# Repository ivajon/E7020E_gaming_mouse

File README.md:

# Awesome gaming mouse
The awesome gaming mouse project, the one mouse to rule them all. The schematics
are available [here](schematics_and_pcb). The firmware for the mouse is written in rust using [rtic](https://rtic.rs/) and is found [here](code/e7020e_rtic) the rtic app is in the example [rtic_simple_mouse](code/e7020e_rtic/examples/rtic_simple_mouse.rs). The program used to configure the mouse is found [here](code/hosted/rust_version).

## How to flash the mouse
To flash the mouse read [this](e7020e-project/code/e7020_rtic/README.md) to get the build dependecies. When the dependencis are in place it can be built, flashed and run with `cargo run --example rtic_simple_mouse --release`. Note! it can't be built in debug mode since this will create to big of a binary and will not fit on the flash of a stm32f401re.

## Members

- Erik Serrander
- eriser-8@student.ltu.se
  
- Ivar Jönsson
- ivajns-9@student.ltu.se

## High level specification

### Basic
- [x] Left and right click
- [x] relative position

### Higher
- [x] scroll wheel
- [x] macro system
- [x] Side buttons

### Stretch
- [x] Computer communication
- [ ] LEDs, i.e. debug/ui
- [ ] Rumble motor
- [ ] Perfect spray

### Implementation
- Unit testing
- Cuntinuous integration

# Specifications
## Mouse buttons
The buttons used are [D2F-01F](https://www.elfa.se/sv/mikrobrytare-d2f-100ma-1co-74n-kolv-omron-electronic-components-d2f-01f/p/11082662?track=true&no-cache=true&marketingPopup=false) since these are well regarded by users.
We have decided to have 4 main buttons on the mouse, 2 on the front and 2 on the side.
## Side buttons 

To reduce the bouncing of the buttons a 10u capacitor is places to ground from the signal trace. This will allow the signal to be pulled low for high frequencies. 

To drive the buttons a 5v voltage is used with a series resistor of 4.7 k to limit the current to close to 1mA. The mosfet used to limit the output acts as a decoupler thus not draining anny current ( in theory ).

## Front buttons

## Mouse wheel

The [mouse wheel](https://se.rs-online.com/web/p/mechanical-rotary-encoders/7295545) is also debounced using the same capacitor values as the mouse button. This should not be as needed but better safe than sorry.

The mouse wheel also uses the same nfet to step down the voltage.

## Rumble motor

## Main board

## Case 
We will base our case on this moddel of the [g305](https://www.thingiverse.com/thing:3969266)
with this [base](https://www.thingiverse.com/thing:3564894).

The stl files can be found in our [model folder](model/).

## Grading

- Erik Serrander
  - Expected contributions towards grade 4
    - side buttons
    - diodes
  - Expected contributions towards grade 5
    - Computer communication
    - Rumble motor
  
- Ivar Jönsson
  - Expected contributions towards grade 4
    - PCB layout
      - Itterative design using a 3d printer to validate pcb fitting and footprint layout
      - Ease of assembly
    - Case customization 
      - Mountingholes and posibility to use a usb cable
    - Mouse wheel
      - Selecting a rotary encoder
    - diodes
      - status LEDs to validate voltage sections
  - Expected contributions towards grade 5
    - Computer communication
    - DPI configuration
    - Perfect spray
      - This might not be applicable. 

## contributions

- Erik Serrander
  - Hardware design (werry minor)
  - Macro system
  - Macro system config mouse side
  - Mouse state software (major)

- Ivar Jönsson
  - Hardware design (allmost all)
  - Macro system config pc side
  - Mouse state software (minor)
  - Enclosure manufacturing

- Togheter / both
  - Init code
  - Interuppt handlers
  - Harware assembly

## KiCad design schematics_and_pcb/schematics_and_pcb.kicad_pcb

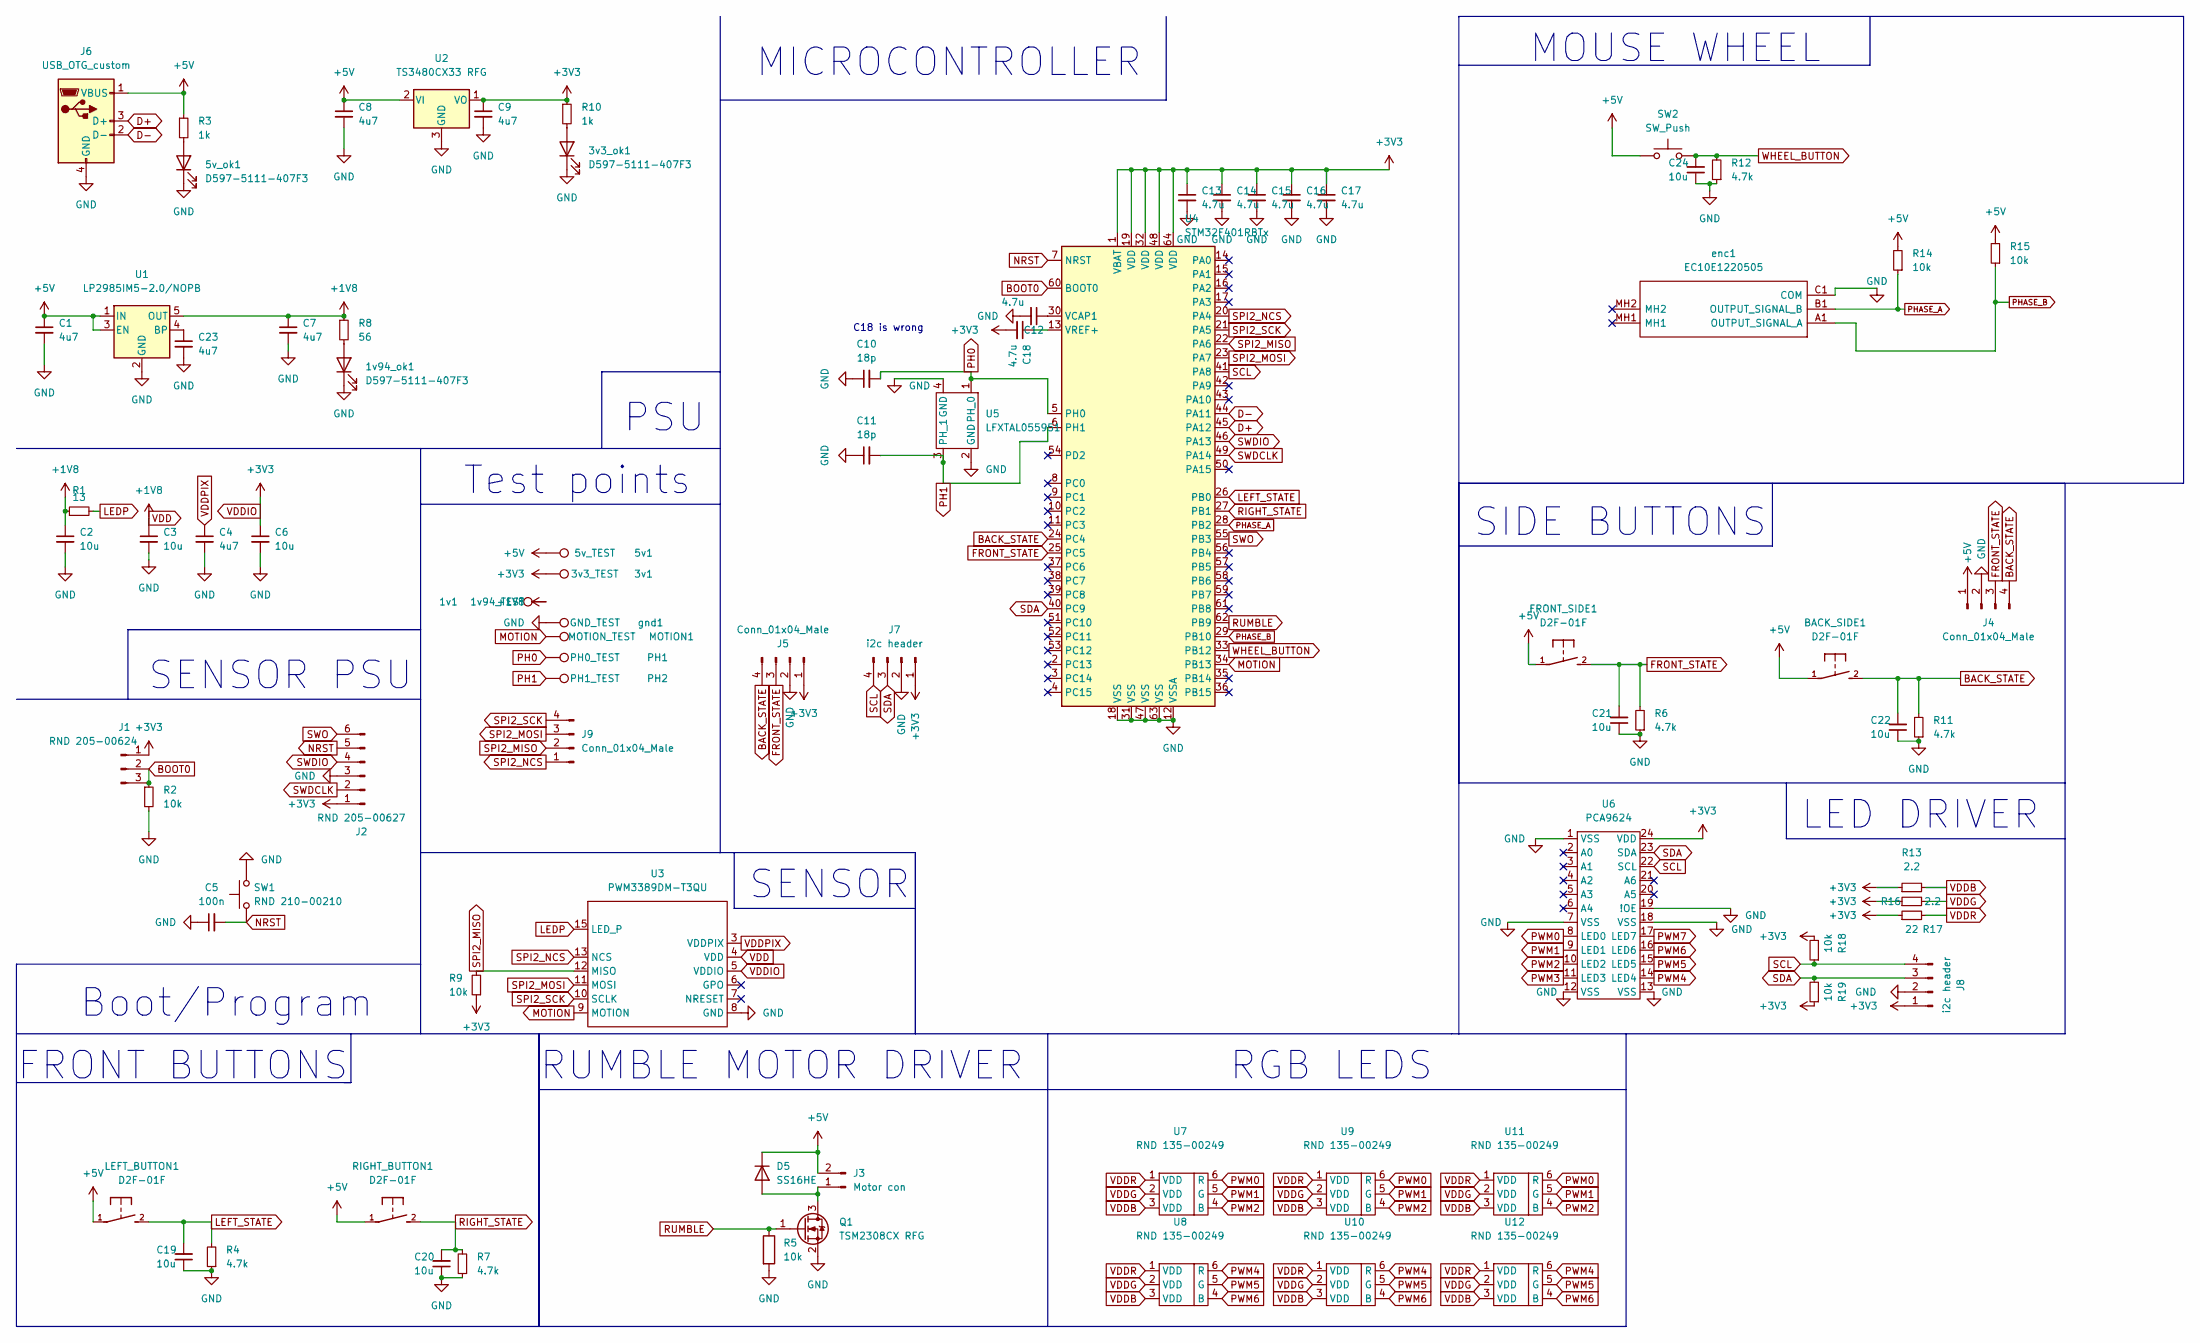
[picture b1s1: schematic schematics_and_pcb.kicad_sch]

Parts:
1v1: 1v94_TEST; PinHeader_1x01_P2.54mm_Vertical
1v94_ok1, 3v3_ok1, 5v_ok1: D597-5111-407F3; LED_0805_2012Metric_Pad1.15x1.40mm_HandSolder; part # D597-5111-407F3
3v1: 3v3_TEST; PinHeader_1x01_P2.54mm_Vertical
5v1: 5v_TEST; PinHeader_1x01_P2.54mm_Vertical
BACK_SIDE1: D2F-01F
C1, C4, C7, C8, C9, C23: 4u7; C_0805_2012Metric_Pad1.18x1.45mm_HandSolder
C2, C3, C6, C19, C20, C21, C22, C24: 10u; C_0805_2012Metric_Pad1.18x1.45mm_HandSolder
C5: 100n; C_0805_2012Metric_Pad1.18x1.45mm_HandSolder
C10, C11: 18p; C_0805_2012Metric_Pad1.18x1.45mm_HandSolder
C12, C13, C14, C15, C16, C17, C18: 4.7u; C_0805_2012Metric_Pad1.18x1.45mm_HandSolder
D5: SS16HE; SOD-323HE; part # SS16HE
FRONT_SIDE1: D2F-01F
J1: RND 205-00624; PinHeader_1x03_P2.54mm_Vertical
J2: RND 205-00627; PinHeader_1x06_P2.54mm_Vertical
J3: Motor con; PinSocket_1x02_P2.54mm_Vertical
J4, J5: Conn_01x04_Male; PinHeader_1x04_P2.54mm_Vertical
J6: USB_OTG_custom; USB_2.45
J7, J8: i2c header; PinHeader_1x04_P2.54mm_Vertical
J9: Conn_01x04_Male; PinHeader_1x04_P1.00mm_Vertical
LEFT_BUTTON1: D2F-01F; part # D2F-01F
MOTION1: MOTION_TEST; PinHeader_1x01_P2.54mm_Vertical
PH1: PH0_TEST; PinHeader_1x01_P2.54mm_Vertical
PH2: PH1_TEST; PinHeader_1x01_P2.54mm_Vertical
Q1: TSM2308CX RFG; SOT-23; part # TSM2308CX RFG
R1: 13; R_0805_2012Metric_Pad1.20x1.40mm_HandSolder; part # RND 155HP05W3F130JT5E
R2, R9, R14, R15, R18, R19: 10k; R_0805_2012Metric_Pad1.20x1.40mm_HandSolder; part # RT0805FRE0710KL
R3, R10: 1k; R_0805_2012Metric_Pad1.20x1.40mm_HandSolder; part # RC0805FR-071KL
R4, R6, R7, R11, R12: 4.7k; R_0805_2012Metric_Pad1.20x1.40mm_HandSolder; part # RC0805FR-074K7L
R5: 10k; R_0805_2012Metric_Pad1.20x1.40mm_HandSolder; part # RC0805FR-071KL
R8: 56; R_0805_2012Metric_Pad1.20x1.40mm_HandSolder; part # RND 155HP05W3F560JT5E
R13, R16: 2.2; R_0805_2012Metric_Pad1.20x1.40mm_HandSolder
R17: 22; R_0805_2012Metric_Pad1.20x1.40mm_HandSolder
RIGHT_BUTTON1: D2F-01F; part # D2F-01F
SW1: RND 210-00210; SW_Push_1P1T_NO_6x6mm_H9.5mm
SW2: SW_Push; evqP0E07; part # evqP0E07
U1: LP2985IM5-2.0/NOPB; SOT-23-5; part # LP2985IM5-2.0/NOPB
U2: TS3480CX33 RFG; SOT-23; part # TS3480CX33 RFG
U3: PWM3389DM-T3QU; PMW3389DM-T3QU; part # PWM3389DM-T3QU
U4: STM32F401RBTx; LQFP-64_10x10mm_P0.5mm
U5: LFXTAL055951
U6: PCA9624; TSSOP-24
U7, U8, U9, U10, U11, U12: RND 135-00249; RND_135-00249
enc1: EC10E1220505; Manufacturer_Part_Number EC10E1220505; Mouser Part Number 688-EC10E1220505
gnd1: GND_TEST; PinHeader_1x01_P2.54mm_Vertical

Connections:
+5V: 5v1.1, BACK_SIDE1.1, C1.1, C8.1, D5.1 (K), FRONT_SIDE1.1, J3.2, J4.1, J6.1 (VBUS), LEFT_BUTTON1.1, R3.1, R14.2, R15.2, RIGHT_BUTTON1.1, SW2.1, U1.1 (IN), U1.3 (EN), U2.2 (VI)
BACK_STATE: BACK_SIDE1.2, C22.2, J4.4, J5.4, R11.2, U4.24 (PC4)
BOOT0: J1.2, J1.3, R2.1, U4.60 (BOOT0)
D+: J6.3 (D+), U4.45 (PA12)
D-: J6.2 (D-), U4.44 (PA11)
FRONT_STATE: C21.2, FRONT_SIDE1.2, J4.3, J5.3, R6.2, U4.25 (PC5)
GND: 1v94_ok1.1 (K), 3v3_ok1.1 (K), 5v_ok1.1 (K), C1.2, C2.2, C3.2, C4.2, C5.1, C6.2, C7.2, C8.2, C9.2, C10.1, C11.1, C12.2, C13.2, C14.2, C15.2, C16.2, C17.2, C19.1, C20.1, C21.1, C22.1, C23.2, C24.1, J2.3, J4.2, J5.2, J6.4 (GND), J7.2, J8.2, Q1.2 (S), R2.2, R4.1, R5.2, R6.1, R7.1, R11.1, R12.1, SW1.2, U1.2 (GND), U2.3 (GND), U3.8 (GND), U4.12 (VSSA), U4.18 (VSS), U4.31 (VSS), U4.47 (VSS), U4.63 (VSS), U5.2 (GND), U5.4 (GND), U6.1 (VSS), U6.7 (VSS), U6.12 (VSS), U6.13 (VSS), U6.18 (VSS), U6.19 (!OE), enc1.C1 (COM), gnd1.1
LEDP: R1.2, U3.15 (LED_P)
LEFT_STATE: C19.2, LEFT_BUTTON1.2, R4.2, U4.26 (PB0)
MOTION: MOTION1.1, U3.9 (MOTION), U4.34 (PB13)
NRST: C5.2, J2.5, SW1.1, U4.7 (NRST)
unnamed: 1v94_ok1.2 (A), R8.2
unnamed: 3v3_ok1.2 (A), R10.2
unnamed: 5v_ok1.2 (A), R3.2
unnamed: C12.1, U4.30 (VCAP1)
unnamed: C18.1, U4.13 (VREF+)
unnamed: C23.1, U1.4 (BP)
unnamed: D5.2 (A), J3.1, Q1.3 (D)
PH0: C10.2, PH1.1, U4.5 (PH0), U5.1 (PH_0)
PH1: C11.2, PH2.1, U4.6 (PH1), U5.3 (PH_1)
PHASE_A: R14.1, U4.28 (PB2), enc1.B1 (OUTPUT_SIGNAL_B)
PHASE_B: R15.1, U4.29 (PB10), enc1.A1 (OUTPUT_SIGNAL_A)
PWM0: U6.8 (LED0), U7.6 (R), U9.6 (R), U11.6 (R)
PWM1: U6.9 (LED1), U7.5 (G), U9.5 (G), U11.5 (G)
PWM2: U6.10 (LED2), U7.4 (B), U9.4 (B), U11.4 (B)
PWM3: U6.11 (LED3)
PWM4: U6.14 (LED4), U8.6 (R), U10.6 (R), U12.6 (R)
PWM5: U6.15 (LED5), U8.5 (G), U10.5 (G), U12.5 (G)
PWM6: U6.16 (LED6), U8.4 (B), U10.4 (B), U12.4 (B)
PWM7: U6.17 (LED7)
RIGHT_STATE: C20.2, R7.2, RIGHT_BUTTON1.2, U4.27 (PB1)
RUMBLE: Q1.1 (G), R5.1, U4.62 (PB9)
SCL: J7.4, J8.4, R18.1, U4.41 (PA8), U6.22 (SCL)
SDA: J7.3, J8.3, R19.2, U4.40 (PC9), U6.23 (SDA)
SPI2_MISO: J9.2, R9.2, U3.12 (MISO), U4.22 (PA6)
SPI2_MOSI: J9.3, U3.11 (MOSI), U4.23 (PA7)
SPI2_NCS: J9.1, U3.13 (NCS), U4.20 (PA4)
SPI2_SCK: J9.4, U3.10 (SCLK), U4.21 (PA5)
SWDCLK: J2.2, U4.49 (PA14)
SWDIO: J2.4, U4.46 (PA13)
SWO: J2.6, U4.55 (PB3)
VDD: 1v1.1, C2.1, C3.1, C7.1, R1.1, R8.1, U1.5 (OUT), U3.4 (VDD)
VDDB: R13.2, U7.3 (VDD), U8.3 (VDD), U9.3 (VDD), U10.3 (VDD), U11.3 (VDD), U12.3 (VDD)
VDDG: R16.2, U7.2 (VDD), U8.2 (VDD), U9.2 (VDD), U10.2 (VDD), U11.2 (VDD), U12.2 (VDD)
VDDIO: 3v1.1, C6.1, C9.1, C13.1, C14.1, C15.1, C16.1, C17.1, C18.2, J1.1, J2.1, J5.1, J7.1, J8.1, R9.1, R10.1, R13.1, R16.1, R17.1, R18.2, R19.1, U2.1 (VO), U3.5 (VDDIO), U4.1 (VBAT), U4.19 (VDD), U4.32 (VDD), U4.48 (VDD), U4.64 (VDD), U6.24 (VDD)
VDDPIX: C4.1, U3.3 (VDDPIX)
VDDR: R17.2, U7.1 (VDD), U8.1 (VDD), U9.1 (VDD), U10.1 (VDD), U11.1 (VDD), U12.1 (VDD)
WHEEL_BUTTON: C24.2, R12.2, SW2.2, U4.33 (PB12)

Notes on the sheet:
LED DRIVER
Test points
PSU
SENSOR
C18 is wrong
FRONT BUTTONS
Boot/Program
SENSOR PSU
RGB LEDS
MICROCONTROLLER
RUMBLE MOTOR DRIVER
MOUSE WHEEL
SIDE BUTTONS

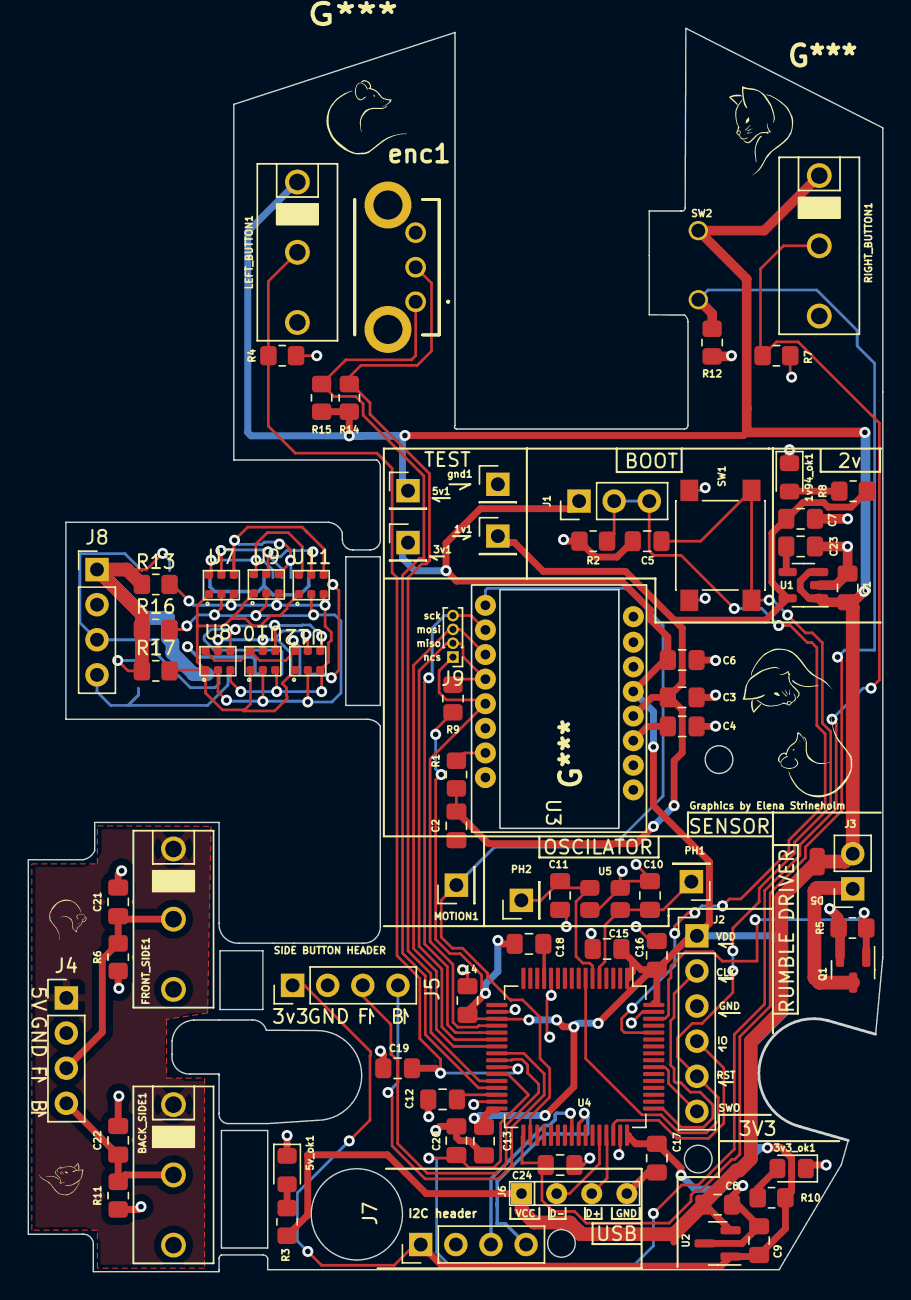
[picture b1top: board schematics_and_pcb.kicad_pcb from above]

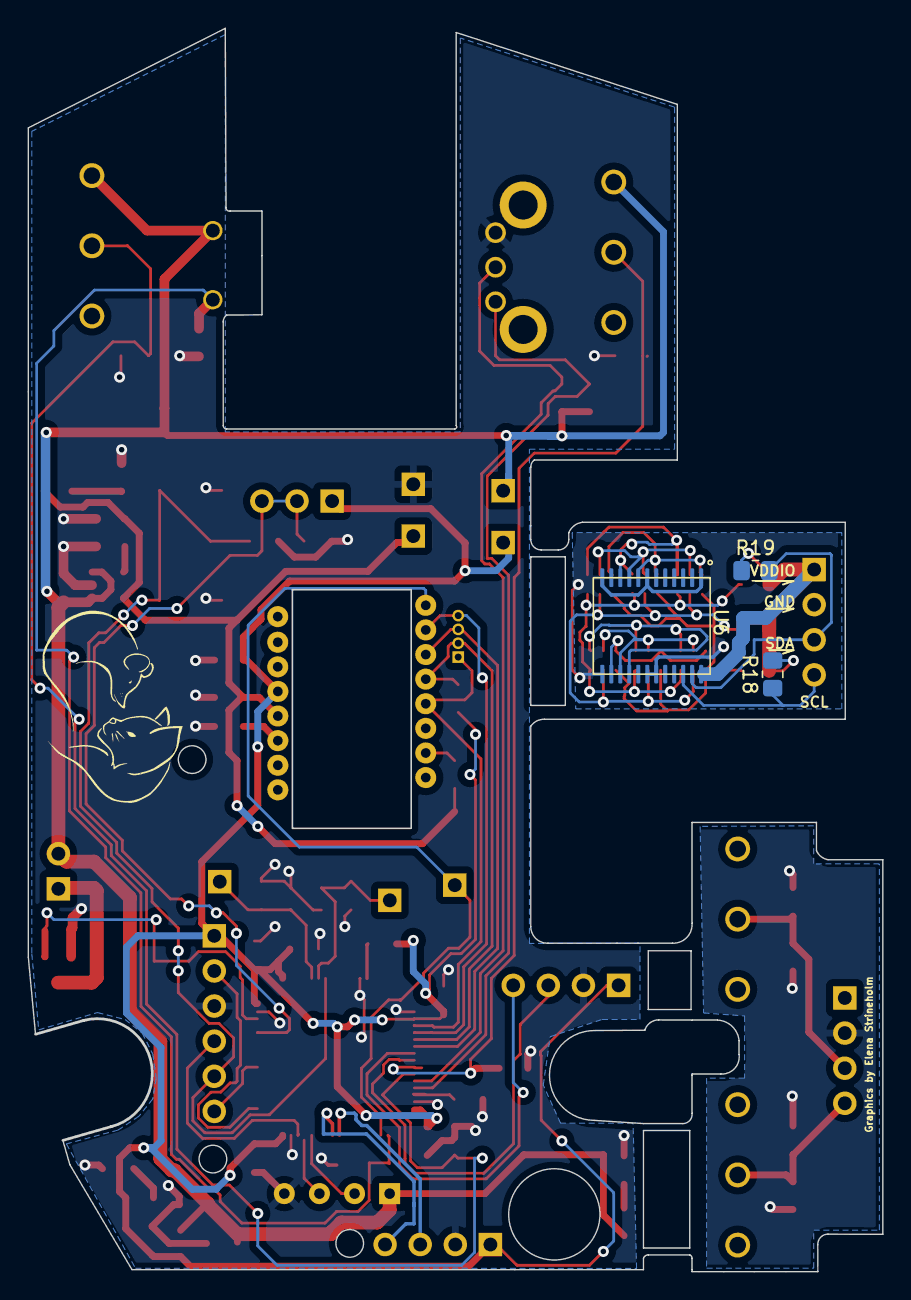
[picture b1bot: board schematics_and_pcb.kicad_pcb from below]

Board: 2 copper layers, 61.8 x 89.9 mm, 83 parts (3 on the bottom side), 46 nets.

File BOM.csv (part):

Source:,/home/ivarj/git/project/e7020e-project/schematics_and_pcb/schematics_and_pcb.kicad_sch
Date:,fre 11 feb 2022 14:17:39
Tool:,Eeschema (6.0.1)
Generator:,/usr/share/kicad/plugins/bom_csv_grouped_by_value.py
Component Count:,82
,
Individual Components:,
,
Item,Qty,Reference(s),Value,LibPart,Footprint,Datasheet,Description,Height,Manufacturer_Name,Manufacturer_Part_Number,Mouser Part Number,Mouser Price/Stock,part #
,,1v1,1v94_TEST,Connector:TestPoint,Connector_PinHeader_2.54mm:PinHeader_1x01_P2.54mm_Vertical,~,,,,,,,
,,1v94_ok1,D597-5111-407F3,Device:LED,LED_SMD:LED_0805_2012Metric_Pad1.15x1.40mm_HandSolder,~,,,,,,,D597-5111-407F3
,,3v1,3v3_TEST,Connector:TestPoint,Connector_PinHeader_2.54mm:PinHeader_1x01_P2.54mm_Vertical,~,,,,,,,
,,3v3_ok1,D597-5111-407F3,Device:LED,LED_SMD:LED_0805_2012Metric_Pad1.15x1.40mm_HandSolder,~,,,,,,,D597-5111-407F3
,,5v1,5v_TEST,Connector:TestPoint,Connector_PinHeader_2.54mm:PinHeader_1x01_P2.54mm_Vertical,~,,,,,,,
,,5v_ok1,D597-5111-407F3,Device:LED,LED_SMD:LED_0805_2012Metric_Pad1.15x1.40mm_HandSolder,~,,,,,,,D597-5111-407F3
,,BACK_SIDE1,D2F-01F,mouse:D2F-01F,mouse:D2F-01F,,,,,,,,
,,C1,4u7,Device:C_Small,Capacitor_SMD:C_0805_2012Metric_Pad1.18x1.45mm_HandSolder,~,,,,,,,
,,C2,10u,Device:C_Small,Capacitor_SMD:C_0805_2012Metric_Pad1.18x1.45mm_HandSolder,~,,,,,,,
,,C3,10u,Device:C_Small,Capacitor_SMD:C_0805_2012Metric_Pad1.18x1.45mm_HandSolder,~,,,,,,,
,,C4,4u7,Device:C_Small,Capacitor_SMD:C_0805_2012Metric_Pad1.18x1.45mm_HandSolder,~,,,,,,,
,,C5,100n,Device:C_Small,Capacitor_SMD:C_0805_2012Metric_Pad1.18x1.45mm_HandSolder,~,,,,,,,
,,C6,10u,Device:C_Small,Capacitor_SMD:C_0805_2012Metric_Pad1.18x1.45mm_HandSolder,~,,,,,,,
,,C7,4u7,Device:C_Small,Capacitor_SMD:C_0805_2012Metric_Pad1.18x1.45mm_HandSolder,~,,,,,,,
,,C8,4u7,Device:C_Small,Capacitor_SMD:C_0805_2012Metric_Pad1.18x1.45mm_HandSolder,~,,,,,,,
,,C9,4u7,Device:C_Small,Capacitor_SMD:C_0805_2012Metric_Pad1.18x1.45mm_HandSolder,~,,,,,,,
,,C10,18p,Device:C_Small,Capacitor_SMD:C_0805_2012Metric_Pad1.18x1.45mm_HandSolder,~,,,,,,,
,,C11,18p,Device:C_Small,Capacitor_SMD:C_0805_2012Metric_Pad1.18x1.45mm_HandSolder,~,,,,,,,
,,C12,4.7u,Device:C_Small,Capacitor_SMD:C_0805_2012Metric_Pad1.18x1.45mm_HandSolder,~,,,,,,,
,,C13,4.7u,Device:C_Small,Capacitor_SMD:C_0805_2012Metric_Pad1.18x1.45mm_HandSolder,~,,,,,,,
,,C14,4.7u,Device:C_Small,Capacitor_SMD:C_0805_2012Metric_Pad1.18x1.45mm_HandSolder,~,,,,,,,
,,C15,4.7u,Device:C_Small,Capacitor_SMD:C_0805_2012Metric_Pad1.18x1.45mm_HandSolder,~,,,,,,,
,,C16,4.7u,Device:C_Small,Capacitor_SMD:C_0805_2012Metric_Pad1.18x1.45mm_HandSolder,~,,,,,,,
,,C17,4.7u,Device:C_Small,Capacitor_SMD:C_0805_2012Metric_Pad1.18x1.45mm_HandSolder,~,,,,,,,
,,C18,4.7u,Device:C_Small,Capacitor_SMD:C_0805_2012Metric_Pad1.18x1.45mm_HandSolder,~,,,,,,,
,,C19,10u,Device:C_Small,Capacitor_SMD:C_0805_2012Metric_Pad1.18x1.45mm_HandSolder,~,,,,,,,
,,C20,10u,Device:C_Small,Capacitor_SMD:C_0805_2012Metric_Pad1.18x1.45mm_HandSolder,~,,,,,,,
,,C21,10u,Device:C_Small,Capacitor_SMD:C_0805_2012Metric_Pad1.18x1.45mm_HandSolder,~,,,,,,,
,,C22,10u,Device:C_Small,Capacitor_SMD:C_0805_2012Metric_Pad1.18x1.45mm_HandSolder,~,,,,,,,
,,C23,4u7,Device:C_Small,Capacitor_SMD:C_0805_2012Metric_Pad1.18x1.45mm_HandSolder,~,,,,,,,
,,C24,10u,Device:C_Small,Capacitor_SMD:C_0805_2012Metric_Pad1.18x1.45mm_HandSolder,~,,,,,,,
,,D5,SS16HE,Diode:1N4001,mouse:SOD-323HE,http://www.vishay.com/docs/88503/1n4001.pdf,,,,,,,SS16HE
,,enc1,EC10E1220505,mouse:EC10E1220505,mouse:EC10E1220505,https://tech.alpsalpine.com/prod/e/html/encoder/incremental/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,10mm Size Hollow Shaft Type EC10E Incremental Encoder,10.6,ALPS Electric,EC10E1220505,688-EC10E1220505,https://www.mouser.co.uk/ProductDetail/Alps-Alpine/EC10E1220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,
,,FRONT_SIDE1,D2F-01F,mouse:D2F-01F,mouse:D2F-01F,,,,,,,,
,,gnd1,GND_TEST,Connector:TestPoint,Connector_PinHeader_2.54mm:PinHeader_1x01_P2.54mm_Vertical,~,,,,,,,
,,J1,RND 205-00624,Connector:Conn_01x03_Male,Connector_PinHeader_2.54mm:PinHeader_1x03_P2.54mm_Vertical,~,,,,,,,
,,J2,RND 205-00627,Connector:Conn_01x06_Male,Connector_PinHeader_2.54mm:PinHeader_1x06_P2.54mm_Vertical,~,,,,,,,
,,J3,Motor con,Connector:Conn_01x02_Male,Connector_PinSocket_2.54mm:PinSocket_1x02_P2.54mm_Vertical,~,,,,,,,
,,J4,Conn_01x04_Male,Connector:Conn_01x04_Male,Connector_PinHeader_2.54mm:PinHeader_1x04_P2.54mm_Vertical,~,,,,,,,
,,J5,Conn_01x04_Male,Connector:Conn_01x04_Male,Connector_PinHeader_2.54mm:PinHeader_1x04_P2.54mm_Vertical,~,,,,,,,
,,J6,USB_OTG_custom,mouse:USB_OTG_custom,mouse:USB_2.45, ~,,,,,,,
,,J7,i2c header,Connector:Conn_01x04_Male,Connector_PinHeader_2.54mm:PinHeader_1x04_P2.54mm_Vertical,~,,,,,,,
,,J8,i2c header,Connector:Conn_01x04_Male,Connector_PinHeader_2.54mm:PinHeader_1x04_P2.54mm_Vertical,~,,,,,,,
,,LEFT_BUTTON1,D2F-01F,mouse:D2F-01F,mouse:D2F-01F,,,,,,,,D2F-01F
,,MOTION1,MOTION_TEST,Connector:TestPoint,Connector_PinHeader_2.54mm:PinHeader_1x01_P2.54mm_Vertical,~,,,,,,,
,,PH1,PH0_TEST,Connector:TestPoint,Connector_PinHeader_2.54mm:PinHeader_1x01_P2.54mm_Vertical,~,,,,,,,
,,PH2,PH1_TEST,Connector:TestPoint,Connector_PinHeader_2.54mm:PinHeader_1x01_P2.54mm_Vertical,~,,,,,,,
,,Q1,TSM2308CX RFG,Device:Q_NMOS_GSD,Package_TO_SOT_SMD:SOT-23,~,,,,,,,TSM2308CX RFG
,,R1,13,Device:R_Small,Resistor_SMD:R_0805_2012Metric_Pad1.20x1.40mm_HandSolder,~,,,,,,,RND 155HP05W3F130JT5E
,,R2,10k,Device:R_Small,Resistor_SMD:R_0805_2012Metric_Pad1.20x1.40mm_HandSolder,~,,,,,,,RT0805FRE0710KL
,,R3,1k,Device:R_Small,Resistor_SMD:R_0805_2012Metric_Pad1.20x1.40mm_HandSolder,~,,,,,,,RC0805FR-071KL
,,R4,4.7k,Device:R_Small,Resistor_SMD:R_0805_2012Metric_Pad1.20x1.40mm_HandSolder,~,,,,,,,RC0805FR-074K7L
,,R5,10k,Device:R,Resistor_SMD:R_0805_2012Metric_Pad1.20x1.40mm_HandSolder,~,,,,,,,RC0805FR-071KL
,,R6,4.7k,Device:R_Small,Resistor_SMD:R_0805_2012Metric_Pad1.20x1.40mm_HandSolder,~,,,,,,,RC0805FR-074K7L
,,R7,4.7k,Device:R_Small,Resistor_SMD:R_0805_2012Metric_Pad1.20x1.40mm_HandSolder,~,,,,,,,RC0805FR-074K7L
,,R8,56,Device:R_Small,Resistor_SMD:R_0805_2012Metric_Pad1.20x1.40mm_HandSolder,~,,,,,,,RND 155HP05W3F560JT5E
,,R9,10k,Device:R_Small,Resistor_SMD:R_0805_2012Metric_Pad1.20x1.40mm_HandSolder,~,,,,,,,RT0805FRE0710KL
,,R10,1k,Device:R_Small,Resistor_SMD:R_0805_2012Metric_Pad1.20x1.40mm_HandSolder,~,,,,,,,RC0805FR-071KL
,,R11,4.7k,Device:R_Small,Resistor_SMD:R_0805_2012Metric_Pad1.20x1.40mm_HandSolder,~,,,,,,,RC0805FR-074K7L
,,R12,4.7k,Device:R_Small,Resistor_SMD:R_0805_2012Metric_Pad1.20x1.40mm_HandSolder,~,,,,,,,RC0805FR-074K7L
,,R13,680m,Device:R_Small,Resistor_SMD:R_0805_2012Metric_Pad1.20x1.40mm_HandSolder,~,,,,,,,
,,R14,10k,Device:R_Small,Resistor_SMD:R_0805_2012Metric_Pad1.20x1.40mm_HandSolder,~,,,,,,,RT0805FRE0710KL
,,R15,10k,Device:R_Small,Resistor_SMD:R_0805_2012Metric_Pad1.20x1.40mm_HandSolder,~,,,,,,,RT0805FRE0710KL
,,R16,680m,Device:R_Small,Resistor_SMD:R_0805_2012Metric_Pad1.20x1.40mm_HandSolder,~,,,,,,,
,,R17,8.1999999999999993,Device:R_Small,Resistor_SMD:R_0805_2012Metric_Pad1.20x1.40mm_HandSolder,~,,,,,,,
,,R18,10k,Device:R_Small,Resistor_SMD:R_0805_2012Metric_Pad1.20x1.40mm_HandSolder,~,,,,,,,
,,R19,10k,Device:R_Small,Resistor_SMD:R_0805_2012Metric_Pad1.20x1.40mm_HandSolder,~,,,,,,,RT0805FRE0710KL
,,RIGHT_BUTTON1,D2F-01F,mouse:D2F-01F,mouse:D2F-01F,,,,,,,,D2F-01F
,,SW1,RND 210-00210,Switch:SW_Push,Button_Switch_SMD:SW_Push_1P1T_NO_6x6mm_H9.5mm,~,,,,,,,
,,SW2,SW_Push,Switch:SW_Push,mouse:evqP0E07,~,,,,,,,evqP0E07
,,U1,LP2985IM5-2.0/NOPB,Regulator_Linear:MIC5205-2.5YM5,Package_TO_SOT_SMD:SOT-23-5,https://www.ti.com/lit/ds/symlink/lp2985lv-n.pdf?HQS=dis-mou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,,,,,,,LP2985IM5-2.0/NOPB
,,U2,TS3480CX33 RFG,Regulator_Linear:AP2127N-3.3,Package_TO_SOT_SMD:SOT-23,https://www.diodes.com/assets/Datasheets/AP2127.pdf,,,,,,,TS3480CX33 RFG
,,U3,PWM3389DM-T3QU,mouse:PWM3389DM-T3QU,mouse:PMW3389DM-T3QU,,,,,,,,PWM3389DM-T3QU
,,U4,STM32F401RBTx,MCU_ST_STM32F4:STM32F401RBTx,Package_QFP:LQFP-64_10x10mm_P0.5mm,http://www.st.com/st-web-ui/static/active/en/resource/techni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,,,,,,,
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
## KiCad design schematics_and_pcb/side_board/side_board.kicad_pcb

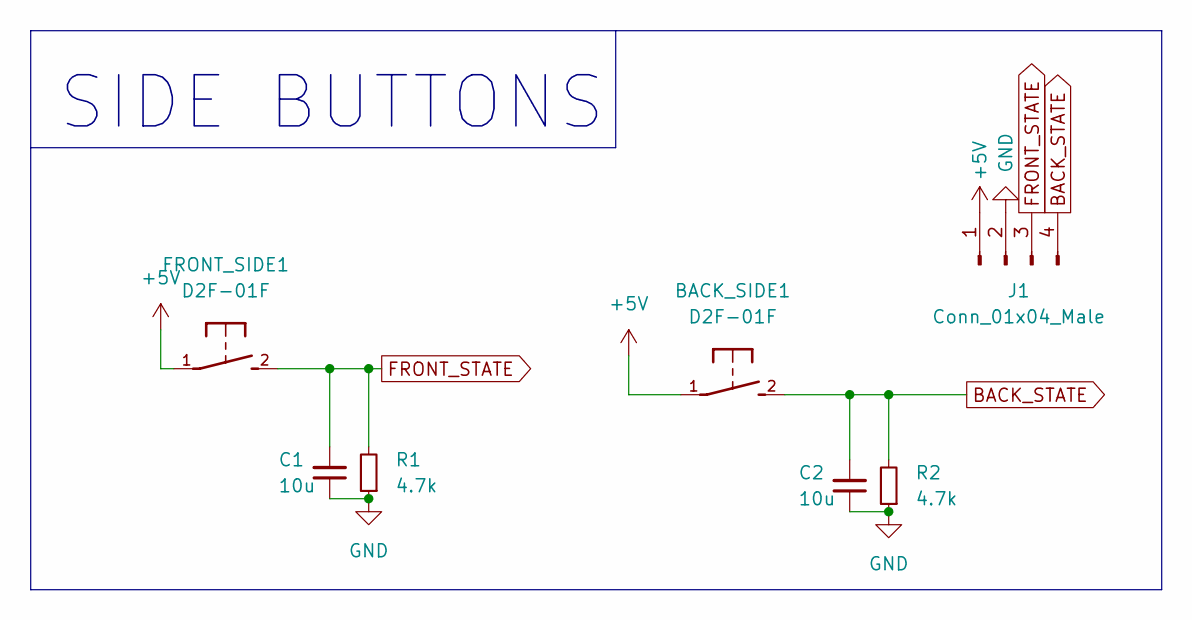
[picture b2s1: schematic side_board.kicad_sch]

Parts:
BACK_SIDE1: D2F-01F
C1, C2: 10u; C_0805_2012Metric_Pad1.18x1.45mm_HandSolder
FRONT_SIDE1: D2F-01F
J1: Conn_01x04_Male; PinHeader_1x04_P2.54mm_Vertical
R1, R2: 4.7k; R_0805_2012Metric_Pad1.20x1.40mm_HandSolder; part # RC0805FR-074K7L

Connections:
+5V: BACK_SIDE1.1, FRONT_SIDE1.1, J1.1
BACK_STATE: BACK_SIDE1.2, C2.2, J1.4, R2.2
FRONT_STATE: C1.2, FRONT_SIDE1.2, J1.3, R1.2
GND: C1.1, C2.1, J1.2, R1.1, R2.1

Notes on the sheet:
SIDE BUTTONS

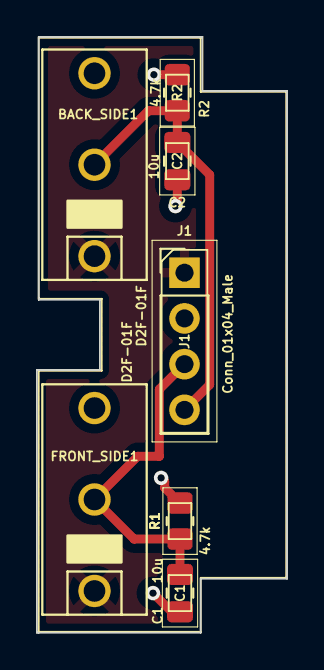
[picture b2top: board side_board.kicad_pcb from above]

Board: 2 copper layers, 13.9 x 33.1 mm, 7 parts (0 on the bottom side), 4 nets.

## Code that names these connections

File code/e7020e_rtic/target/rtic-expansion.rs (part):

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        {
            usb_global : dp.OTG_FS_GLOBAL, usb_device : dp.OTG_FS_DEVICE,
            usb_pwrclk : dp.OTG_FS_PWRCLK, pin_dm :
            gpioa.pa11.into_alternate(), pin_dp : gpioa.pa12.into_alternate(),
            hclk : clocks.hclk(),
        } ; let sck : SCK =
        gpiob.pb3.into_alternate().set_speed(Speed :: VeryHigh) ; let miso :
        MISO = gpiob.pb4.into_alternate().set_speed(Speed :: High) ; let mosi
        : MOSI = gpiob.pb5.into_alternate().set_speed(Speed :: High) ; let cs
        : CS = gpioa.pa4.into_push_pull_output().set_speed(Speed :: High) ;
        let spi : SPI = Spi ::
        new(dp.SPI1, (sck, miso, mosi), MODE_3, 1.MHz(), & clocks) ; let delay
        : DELAY = dp.TIM5.delay_us(& clocks) ; let mut pmw3389 : PMW3389 =
        Pmw3389 :: new(spi, cs, delay).unwrap() ; pmw3389.store_cpi().ok() ;
        let scl : SCL = gpioa.pa8.into_alternate_open_drain() ; let sda : SDA
        = gpioc.pc9.into_alternate_open_drain() ; let mut i2c : I2C = I2c ::
        new(dp.I2C3, (scl, sda), Mode :: from(1.MHz()), & clocks) ; let mut
        interfaces = standard_interfaces() ; let mut rgb_controller :
        PCA9624PW = PCA9624PW :: new(i2c, interfaces, 0xC0) ; let mut
        rgb_pattern_driver = RgbController :: new(rgb_controller) ; let mut
        motion : Button = gpiob.pb13.into_pull_down_input().erase() ; let mut
        phase_a : Button = gpiob.pb2.into_pull_down_input().erase() ; let mut
        phase_b : Button = gpioc.pc10.into_pull_down_input().erase() ; let mut
        left : Button = gpiob.pb0.into_pull_down_input().erase() ; let mut
        right : Button = gpiob.pb1.into_pull_down_input().erase() ; let mut
        middle : Button = gpiob.pb12.into_pull_down_input().erase() ; let mut
        front : Button = gpioc.pc5.into_pull_down_input().erase() ; let mut
        back : Button = gpioc.pc4.into_pull_down_input().erase() ;
        init_button(& mut phase_a, & mut dp.EXTI, Edge :: Rising, & mut
                    sys_cfg) ;
        init_button(& mut phase_b, & mut dp.EXTI, Edge :: Rising, & mut
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
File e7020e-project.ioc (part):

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Mcu.Name=STM32F401R(B-C)Tx
Mcu.Package=LQFP64
Mcu.UserName=STM32F401RBTx
PA11.Mode=Device_Only
PA11.Signal=USB_OTG_FS_DM
PA12.Mode=Device_Only
PA12.Signal=USB_OTG_FS_DP
PA4.Mode=NSS_Signal_Hard_Input
PA4.Signal=SPI1_NSS
PA5.Mode=Full_Duplex_Master
PA5.Signal=SPI1_SCK
PA6.Mode=Full_Duplex_Master
PA6.Signal=SPI1_MISO
PA7.Mode=Full_Duplex_Master
PA7.Signal=SPI1_MOSI
RCC.HSE_VALUE=25000000
RCC.SYSCLKFreq_VALUE=16000000
board=custom

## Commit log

2022-01-19 Added changelog
2022-02-01 added a start point for the design
2022-02-01 prettier lables
2022-02-01 added left and right buttons
2022-02-01 added more buttons and scroll wheel
2022-02-01 added BOM
2022-02-02 Added gitignore
2022-02-02 Added a possible motor drive to schematic.
2022-02-02 added a buttons etc
2022-02-03 added motor driver
2022-02-04 done with main board outline
2022-02-04 main board outline tuned
2022-02-04 some highspeed signal traces
2022-02-04 layout of main board almost done
2022-02-07 new layout
2022-02-07 added mounting holes
2022-02-07 added routes for all signals except buttons and scrollwheel
2022-02-07 added routes for all buttons
2022-02-07 added a logo
2022-02-08 added pin for the rumble
2022-02-08 moved lib
2022-02-08 added new usb symbol
2022-02-08 some fixes
2022-02-08 Added custom usb symbols
2022-02-08 changed to custom usb connector with only 4 pins.
2022-02-08 fixed some drc issues
2022-02-09 filled out the readme
2022-02-09 fixed hotlink
2022-02-09 fixed some of the routing
2022-02-09 added schematic to the readme
2022-02-09 adjusted motor driver resistor
2022-02-10 probs final version
2022-02-11 added RGB LEDS
2022-02-11 some patches
2022-02-11 added pullups
2022-02-11 done with the bom
2022-02-11 updated the bom
2022-03-07 Added code from https://vesuvio-git.neteq.ltu.se/pln/e7020e_rtic .
2022-03-08 stuff
2022-03-09 macro system + skit
2022-03-12 Added a git ignore rule
2022-03-15 this might need to be rolled back
2022-03-15 fixed board
2022-03-15 fixed mouse thing
2022-03-15 bug holding down not working correctly
2022-03-15 added dpi control
2022-03-16 added a small host side program
2022-03-16 cleanup of the host side
2022-03-17 Added new roms and some intercoms
2022-03-17 Macro system probably done
2022-03-18 added comments and a depricated file
2022-03-18 Removed error
2022-03-18 fixed to use right hid descriptor
2022-03-18 removed tracing
2022-03-18 moved sensor to mouse report object
2022-03-18 MacroSystemDone
2022-03-18 fixed small thing
2022-03-18 updated gitignore
2022-03-18 minor modifications
2022-03-18 terminal interface done
2022-03-18 button test
2022-03-20 rgb driver almost done
2022-03-22 modified usb driver, hopefully nothing broke
2022-03-22 added comments to modifiactions
2022-03-23 amen dudå
2022-03-23 removed files precent in gitignore
2022-03-23 Converted to macro system
2022-03-24 fixes
2022-03-25 driver rework
2022-03-25 rebase
2022-03-25 things
2022-03-25 thing
2022-03-25 phase change
2022-03-25 ready
2022-03-25 host almost done
2022-03-25 host side kinda done
2022-03-25 cleanup
2022-03-25 improved mouse
2022-03-25 host end improved
2022-03-26 last minute
2022-03-26 updated config
